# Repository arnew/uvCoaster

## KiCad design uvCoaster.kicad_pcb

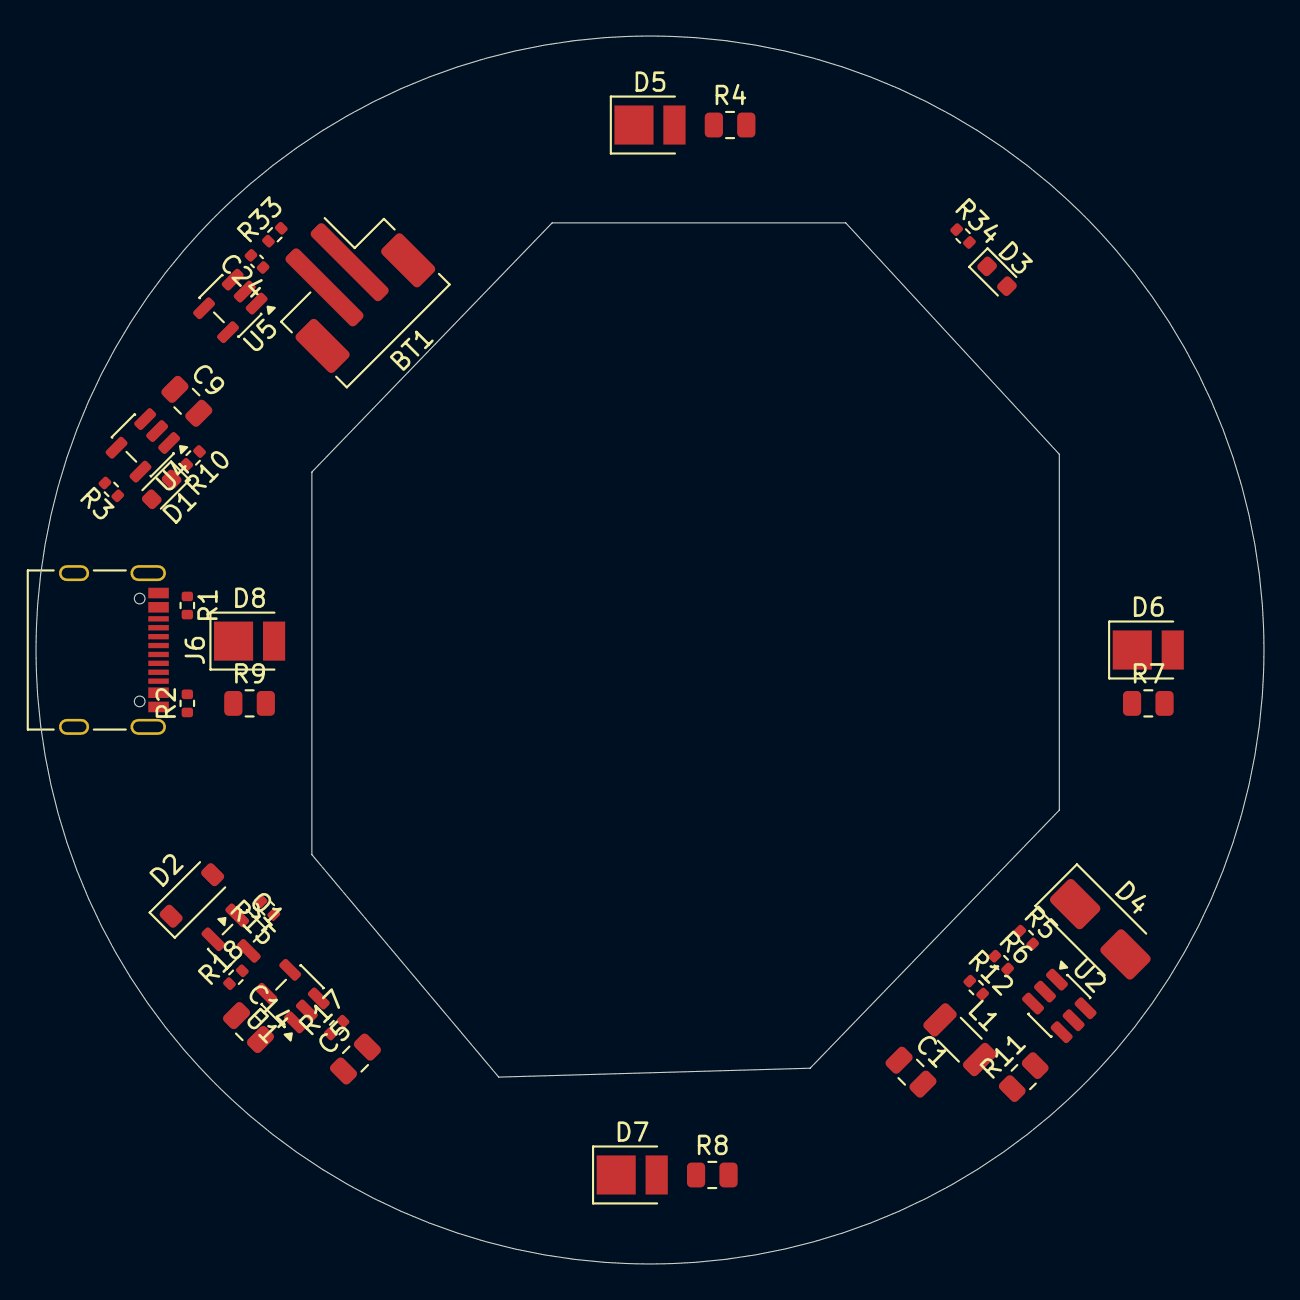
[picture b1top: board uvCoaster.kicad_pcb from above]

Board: 2 copper layers, 69.0 x 69.0 mm, 38 parts (0 on the bottom side), 26 nets, no tracks yet.

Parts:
BT1: Battery_Cell; JST_PH_B2B-PH-SM4-TB_1x02-1MP_P2.00mm_Vertical
C1, C5, C9, C14: 10u; C_0805_2012Metric
C24: 100n; C_0402_1005Metric
D1, D3: LED; LED_0603_1608Metric
D2: MBR0540; D_SOD-123
D4: SS14; D_SMA
D5, D6, D7, D8: P2835P1UVF3G12-365; LED_PLCC_2835
J6: USB_C_Receptacle_USB2.0; USB_C_Receptacle_Palconn_UTC16-G
L1: 6.8uH; L_1206_3216Metric
Q1: DMG3413;AO3401; SOT-23
R1, R2, R3: 5K1; R_0402_1005Metric
R4, R7, R8, R9: 4.7; R_0805_2012Metric
R5: 0; R_0402_1005Metric
R6: R_0402_1005Metric
R10, R12, R15, R34: 10K0; R_0402_1005Metric
R11: 2; R_0805_2012Metric
R17: 3k9; R_0402_1005Metric
R18: 470K; R_0402_1005Metric
R33: 1k; R_0402_1005Metric
U1: AAT4610BIGV-1-T1; SOT-23-5
U2: AP3032KTR; SOT-23-6
U4: MCP73831-2-OT;TP4054-42; SOT-23-5
U5: XB5608G; SOT-23-5

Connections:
+BATT: BT1.1 (+), C9.1, Q1.3 (D), R33.2, U4.3 (VBAT)
-BATT: BT1.2 (-), C24.1, U5.1 (GND), U5.2 (GND)
/SYS_ON: R18.2, U1.4 (ON)
/USB_D+: J6.A6 (D+), J6.B6 (D+)
/USB_D-: J6.A7 (D-), J6.B7 (D-)
GND: C1.2, C5.2, C9.2, C14.2, J6.A1 (GND), J6.A12 (GND), J6.B1 (GND), J6.B12 (GND), R1.1, R2.1, R3.2, R6.1, R11.1, R15.1, R17.1, R34.1, U1.2 (GND), U2.2 (GND), U4.2 (VSS), U5.4 (VM), U5.5 (VM)
unnamed: D1.1 (K), R10.2
unnamed: C14.1, D2.1 (K), Q1.2 (S), R18.1, U1.5 (IN)
unnamed: D3.1 (K), R34.2
unnamed: C1.1, D4.1 (K), R4.2, R5.2, R7.2, R8.2, R9.2
unnamed: D5.2 (A), R4.1
unnamed: D5.1 (K), D6.1 (K), D7.1 (K), D8.1 (K), R11.2, U2.3 (FB)
unnamed: D6.2 (A), R7.1
unnamed: D7.2 (A), R8.1
unnamed: D8.2 (A), R9.1
unnamed: J6.A5 (CC1), R1.2
unnamed: J6.B5 (CC2), R2.2
unnamed: R17.2, U1.3 (SET)
unnamed: R12.1, U2.4 (CTRL)
unnamed: L1.2, U2.6 (V_{IN})
unnamed: R5.1, R6.2, U2.5 (V_{OUT})
unnamed: R3.1, U4.5 (PROG)
unnamed: R10.1, U4.1 (STAT)
unnamed: C24.2, R33.1, U5.3 (VDD)
VBUS: D1.2 (A), D2.2 (A), J6.A4 (VBUS), J6.A9 (VBUS), J6.B4 (VBUS), J6.B9 (VBUS), Q1.1 (G), R15.2, U4.4 (VDD)
VCC: C5.1, D3.2 (A), D4.2 (A), L1.1, R12.2, U1.1 (OUT), U2.1 (SW)

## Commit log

2025-11-01 initial sketch
2025-11-01 preview
2025-11-01 Add MIT License to the project
